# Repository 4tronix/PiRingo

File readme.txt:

PiRingo Python Software

alloff.py	Turns all the LEDs OFF
allon.py	Turns all the LEDs ON
flashdemo.py	Runs through a sequence of flashing/chasing sequences (similar to Kickstarter video)
swing.py	Uses the switches to move a single LED left/right depending which switch is pressed
swing2.py	As swing.py but lights all LEDs in the direction of movement. Winner is the one who gets to the other side!

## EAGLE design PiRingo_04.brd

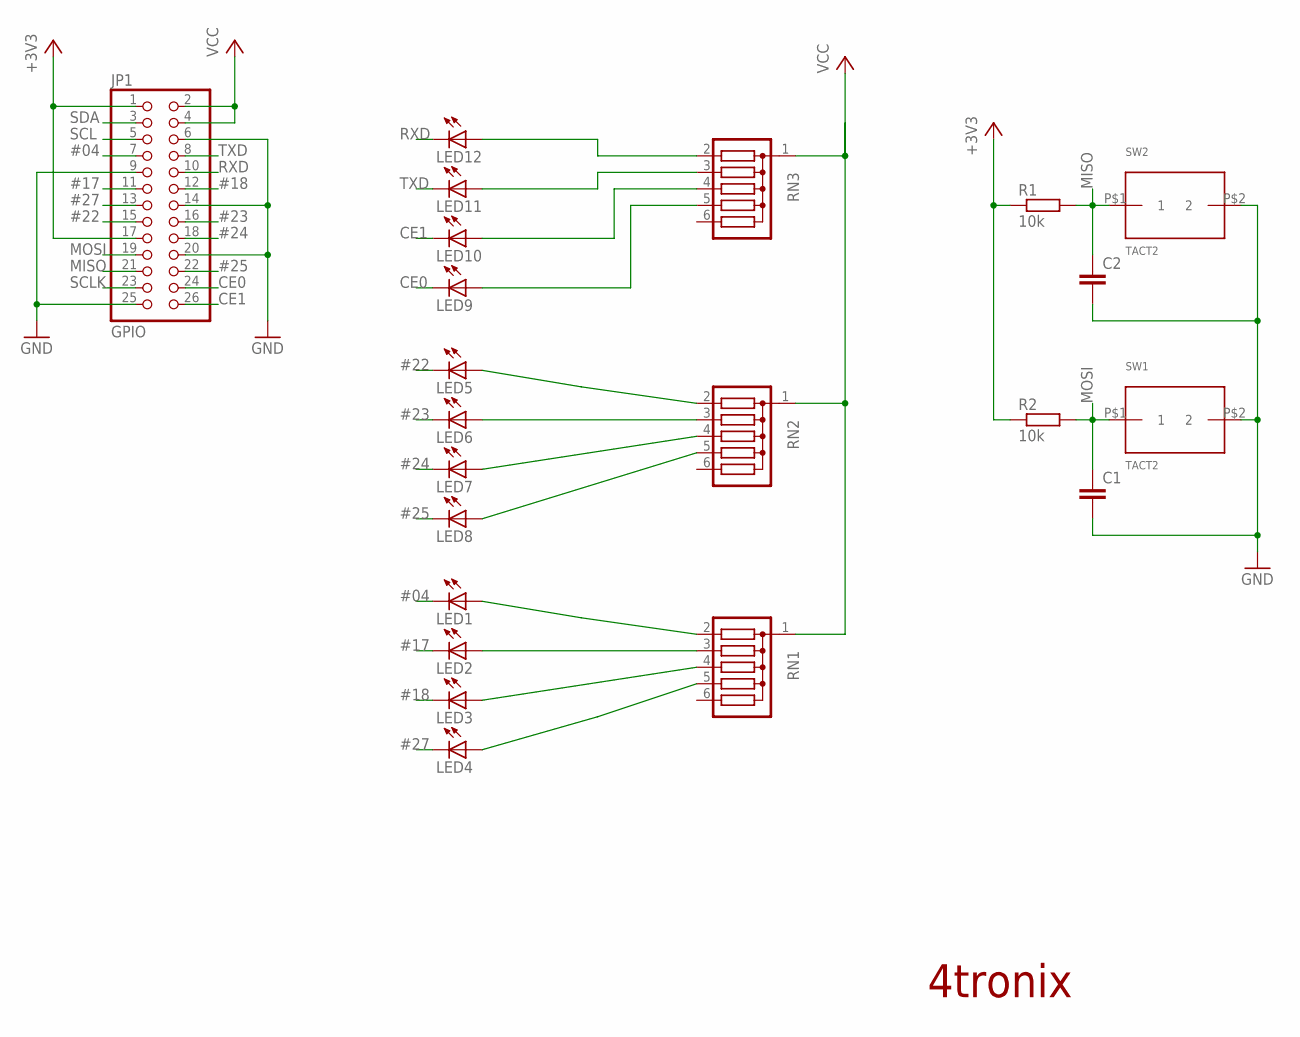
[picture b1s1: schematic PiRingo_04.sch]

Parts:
C1, C2: C5/2.5; C5B2.5
JP1: GPIO; 2X13
LED1, LED2, LED3, LED4, LED5, LED6, LED7, LED8, LED9, LED10, LED11, LED12: LED3MM
R1, R2: 10k; 0207/7
RN1, RN2, RN3: G05R; SIL6
SW1, SW2: TACT2; TACT2-PIN

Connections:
#04: JP1.7, LED1.K (C)
#17: JP1.11, LED2.K (C)
#18: JP1.12, LED3.K (C)
#22: JP1.15, LED5.K (C)
#23: JP1.16, LED6.K (C)
#24: JP1.18, LED7.K (C)
#25: JP1.22, LED8.K (C)
#27: JP1.13, LED4.K (C)
+3V3: JP1.1, JP1.17, R1.1, R2.1
CE0: JP1.24, LED9.K (C)
CE1: JP1.26, LED10.K (C)
GND: C1.2, C2.2, JP1.6, JP1.9, JP1.14, JP1.20, JP1.25, SW1.P$2 (2), SW2.P$2 (2)
MISO: C2.1, JP1.21, R1.2, SW2.P$1 (1)
MOSI: C1.1, JP1.19, R2.2, SW1.P$1 (1)
unnamed: LED12.A, RN3.2
unnamed: LED1.A, RN1.2
unnamed: LED11.A, RN3.3
unnamed: LED10.A, RN3.4
unnamed: LED2.A, RN1.3
unnamed: LED3.A, RN1.4
unnamed: LED4.A, RN1.5
unnamed: LED5.A, RN2.2
unnamed: LED6.A, RN2.3
unnamed: LED7.A, RN2.4
unnamed: LED8.A, RN2.5
unnamed: LED9.A, RN3.5
RXD: JP1.10, LED12.K (C)
SCL: JP1.5
SCLK: JP1.23
SDA: JP1.3
TXD: JP1.8, LED11.K (C)
VCC: JP1.2, JP1.4, RN1.1, RN2.1, RN3.1

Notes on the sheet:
4tronix

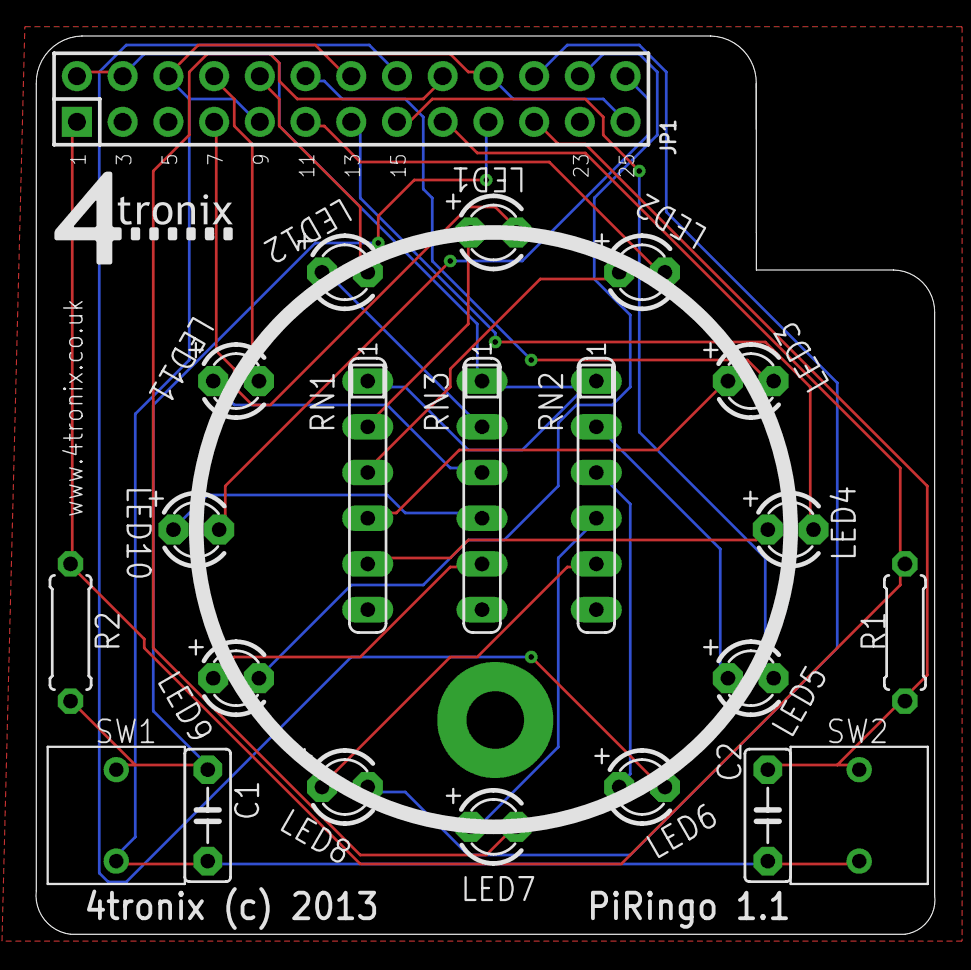
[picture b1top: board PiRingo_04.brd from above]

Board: 2 copper layers, 49.9 x 49.9 mm, 22 parts (0 on the bottom side), 29 nets.

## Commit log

2013-12-01 First Release of Software and Schematic
2013-12-01 Added alloff and schematic pdf
2013-12-12 Added clock.py

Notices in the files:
PiRingo_04.brd:
4tronix (c) 2013
parts and their libraries:
microbuilder: This work is placed in the public domain, and may be freely used for commercial and non-commercial work with the following conditions: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
